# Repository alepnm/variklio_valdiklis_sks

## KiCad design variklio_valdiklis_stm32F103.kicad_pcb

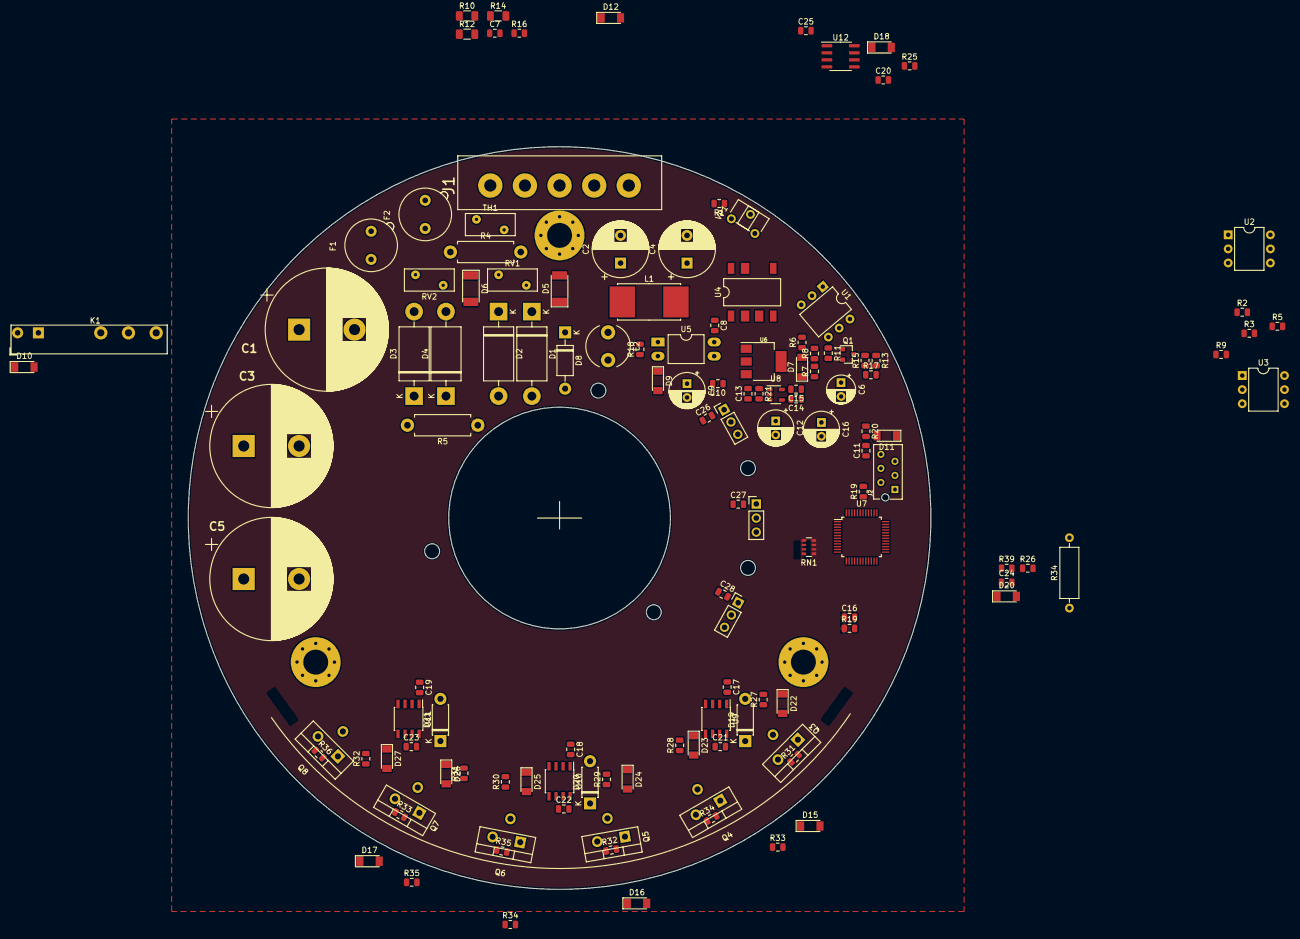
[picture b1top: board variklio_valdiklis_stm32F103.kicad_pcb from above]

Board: 2 copper layers, 134.0 x 134.0 mm, 131 parts (0 on the bottom side), 81 nets, no tracks yet.

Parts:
C1, C3, C5: 120x400V; CP_Radial_D22.0mm_P10.00mm_SnapIn
C2, C4: 4.7x400V; CP_Radial_D10.0mm_P5.00mm
C6: 1.0x50V; CP_Radial_D5.0mm_P2.50mm
C7, C8, C10, C11, C13, C14, C15, C16, C17, C18, C19: 100n; C_0805_2012Metric
C9, C12, C16#2: 100x16V; CP_Radial_D6.3mm_P2.50mm
C20, C24, C25: 1n0; C_0805_2012Metric
C21, C22, C23: 1.0uFx50V; C_0805_2012Metric
C26, C27, C28: 0.1; C_0805_2012Metric
D1, D2, D3, D4: D; D_DO-201AD_P15.24mm_Horizontal
D5, D6: LL4005; D_MELF
D7, D10, D11, D12, D15, D16, D17, D18, D20, D22, D23, D24, D25, D26, D27: LL4148; D_MiniMELF
D8: UF4005; D_DO-41_SOD81_P10.16mm_Horizontal
D9: 12V; D_MiniMELF
D19, D20#2, D21: LL4005; D_DO-41_SOD81_P7.62mm_Horizontal
F1: 5A; Fuseholder_TR5_Littelfuse_No560_No460
F2: 3A; Fuseholder_TR5_Littelfuse_No560_No460
H1: SA; PinHeader_1x03_P2.54mm_Vertical
H2: SB; PinHeader_1x03_P2.54mm_Vertical
H3: SC; PinHeader_1x03_P2.54mm_Vertical
J1: Conn_01x05; Jungtis
J2: ISP_SWD_Connector
K1: Omron; Relay_SPDT_Finder_34.51_Vertical
L1: 1mH; L_Vishay_IHSM-3825
L2: 1mH/280mA; L_Radial_D7.8mm_P5.00mm_Fastron_07HCP
Q1: BC807; SOT-23
Q3, Q4, Q5, Q6, Q7, Q8: IRF830; TO-220-3_Vertical
R1: 1k; R_0805_2012Metric
R2, R9: 1k0; R_0805_2012Metric
R3, R5, R8, R20, R21, R25: 10k; R_0805_2012Metric
R4: 8R2/2W; R_Axial_DIN0411_L9.9mm_D3.6mm_P12.70mm_Horizontal
R5#2: 220k; R_Axial_DIN0411_L9.9mm_D3.6mm_P12.70mm_Horizontal
R6: 490; R_0805_2012Metric
R7: 20k; R_0805_2012Metric
R10, R12, R14: 100k; R_1206_3216Metric
R11: 1M; R_0805_2012Metric
R13: 2.2k; R_0805_2012Metric
R15: 33k; R_0805_2012Metric
R16: 2k2; R_0805_2012Metric
R17: 22k; R_0805_2012Metric
R18: 4k7; R_0805_2012Metric
R19: 100k; R_0805_2012Metric
R19#2, R31#2, R32#2, R33, R34, R35, R36, R39: 1K0; R_0805_2012Metric
R26: 2k0; R_0805_2012Metric
R27, R28, R29, R30, R31, R32: 47R; R_0805_2012Metric
R33#2, R34#3, R35#2: 30R; R_0805_2012Metric
R34#2: 0R1; R_Axial_DIN0309_L9.0mm_D3.2mm_P12.70mm_Horizontal
RN1: 1k0; R_Array_Convex_4x0603
RV1, RV2: Varistor; RV_Disc_D9mm_W4mm_P5mm
TH1: 33R; RV_Disc_D9mm_W4mm_P5mm
U1, U2, U3: CNY17-1; DIP-6_W7.62mm
U4: LNK304G; PowerIntegrations_SMD-8B
U5: PC817; DIP-4_W10.16mm_LongPads
U6: LM340MP-5.0; LM340_SOT-223
U7: STM32F103C8Tx; LQFP-48_7x7mm_P0.5mm
U8: SIP21106; SOT-23-5
U9, U10, U11: IR2101; SOIC-8_3.9x4.9mm_P1.27mm
U12: ACS712; SOIC-8_3.9x4.9mm_P1.27mm
VP1: R_POT_TRIM; Potentiometer_ACP_CA6-H2,5_Horizontal

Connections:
/3VDC: C15.2, C16#2.1, D11.1, D12.1, D20.1, J2.5, R20.1, RN1.5, RN1.6, RN1.7, RN1.8, U2.5, U7.1, U7.9, U7.24, U7.36, U7.48, U8.5
/5VDC: C12.1, C13.2, C25.2, R21.1, U6.3, U8.1, U12.8
/ACL: F1.2, F2.2, J1.1
/ACN: D6.1, J1.2, RV2.2, TH1.2
/ADCVB: C7.2, D12.2, R14.2, R16.2
/CHA: U7.29, U9.2
/CHAN: U7.17, U9.3
/CHB: U7.30, U10.2
/CHBN: U7.18, U10.3
/CHC: U7.31, U11.2
/CHCN: U7.19, U11.3
/CURR: C20.2, D18.1, D20.2, R39.2, U7.13
/OKM: J1.4, U1.2
/OKP: J1.5, R1.2
/PHA: Q3.3, Q4.2, R31#2.1, R33#2.1
/PHB: Q5.3, Q6.2, R32#2.1, R34#3.1
/PHC: Q7.3, Q8.2, R33.1, R35#2.1
/RX: R3.1, U3.4
/RXD: R5.1, U2.4, U7.43
/SA: H1.2, RN1.3, U7.10
/SB: H2.2, RN1.2, U7.11
/SC: H3.2, RN1.1, U7.12
/SPEED: C6.1, R15.1, R17.1, U7.15
/SWDCLK: J2.3, U7.37
/SWDIO: J2.1, U7.34
/TEMP: C16.2, R19#2.2, U7.14
/TXD: R9.1, U7.42
/VB: K1.11, Q3.2, Q5.2, Q7.2
/VCC: C9.1, C10.2, C17.2, C18.2, C19.2, C26.2, C27.2, C28.2, D7.2, D10.1, D15.2, D16.2, D17.2, H1.1, H2.1, H3.1, K1.A1, L2.2, R6.1, R18.2, U5.1, U6.1, U9.1, U10.1, U11.1
/~NRST: C11.2, D11.2, J2.4, R20.2, U7.7
GND: C16.1, R3.2, R5#2.1, R19#2.1, R34#2.1, R39.1, U2.2
GNDD: C1.2, C2.2, C3.2, C4.2, C5.2, C6.2, C7.1, C9.2, C10.1, C11.1, C12.2, C13.1, C14.1, C15.1, C16#2.2, C17.1, C18.1, C19.1, C20.1, C24.1, C25.1, C26.1, C27.1, C28.1, D1.2, D2.2, D6.2, D8.2, D9.2, D19.2, D20#2.2, D21.2, H1.3, H2.3, H3.3, J2.2, J2.6, R5.2, R8.2, R13.2, R16.1, R17.2, R19.2, R25.2, U3.2, U6.2, U7.8, U7.23, U7.35, U7.47, U8.2, U9.4, U10.4, U11.4, U12.3, U12.4, U12.5
unnamed: C1.1, C3.1, C5.1, D3.1, D4.1, K1.14, R5#2.2, R10.1
unnamed: C2.1, D5.1, L1.1
unnamed: C4.1, L1.2, U4.5
unnamed: C8.1, D8.1, L2.1, U4.1, U4.2, U4.7, U4.8
unnamed: C8.2, U4.3, U5.4
unnamed: C14.2, U8.4
unnamed: C21.1, D19.1, R33#2.2, U9.6
unnamed: C21.2, D15.1, U9.8
unnamed: C22.1, D20#2.1, R34#3.2, U10.6
unnamed: C22.2, D16.1, U10.8
unnamed: C23.1, D21.1, R35#2.2, U11.6
unnamed: C23.2, D17.1, U11.8
unnamed: C24.2, U12.6
unnamed: D1.1, D3.2, F1.1, RV1.1
unnamed: D2.1, D4.2, RV1.2, TH1.1
unnamed: D5.2, R4.2
unnamed: D7.1, R7.1
unnamed: D9.1, R18.1, U5.2
unnamed: D10.2, K1.A2
unnamed: D18.2, R25.1, R26.2, R31#2.2
unnamed: D22.1, R27.2, U9.7
unnamed: D22.2, Q3.1, R27.1, R33.2
unnamed: D23.1, R28.2, U9.5
unnamed: D23.2, Q4.1, R28.1, R36.2
unnamed: D24.1, R29.2, U10.7
unnamed: D24.2, Q5.1, R29.1
unnamed: D25.1, R30.2, U10.5
unnamed: D25.2, Q6.1, R30.1
unnamed: D26.1, R31.2, U11.7
unnamed: D26.2, Q7.1, R31.1
unnamed: D27.1, R32.2, U11.5
unnamed: D27.2, Q8.1, R32.1
unnamed: F2.1, R4.1, RV2.1
unnamed: Q1.1, R7.2, R8.1, R11.2
unnamed: Q1.2, R11.1, U1.4
unnamed: Q1.3, R13.1, R15.2
unnamed: R34.1, R34#2.2, R35.1, R36.1
unnamed: Q4.3, Q6.3, Q8.3, U12.1, U12.2
unnamed: R1.1, VP1.1
unnamed: R2.1, U2.1
unnamed: R6.2, U1.5
unnamed: R9.2, U3.1
unnamed: R10.2, R12.1
unnamed: R12.2, R14.1
unnamed: R19.1, U7.44
unnamed: R21.2, U8.3
unnamed: R26.1, U12.7
unnamed: U1.1, VP1.2, VP1.3
unnamed: U4.4, U5.3

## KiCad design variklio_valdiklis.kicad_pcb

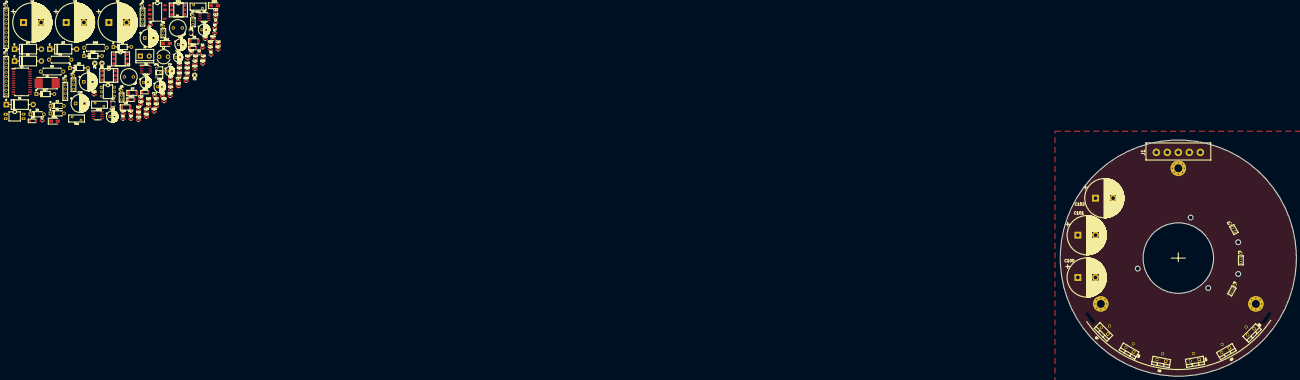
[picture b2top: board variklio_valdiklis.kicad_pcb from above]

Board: 2 copper layers, 134.0 x 134.0 mm, 138 parts (0 on the bottom side), 75 nets, no tracks yet.

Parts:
C1: 22n; C_0805_2012Metric
C2, C4, C6: 120x400V; CP_Radial_D22.0mm_P10.00mm_SnapIn
C3, C5: 4.7x400V; CP_Radial_D10.0mm_P5.00mm
C7: 47n; C_0805_2012Metric
C8, C25: 10n; C_0805_2012Metric
C9: 1.0x50V; CP_Radial_D5.0mm_P2.50mm
C10: 100x16V; CP_Radial_D5.0mm_P2.50mm
C11, C15, C18, C19: 100n; C_0805_2012Metric
C12, C20: 100x16V; CP_Radial_D6.3mm_P2.50mm
C13, C14, C16, C17, C27, C28, C30: 0.1; C_0805_2012Metric
C21, C22, C23: 2n2; C_0805_2012Metric
C24: 4n7; C_0805_2012Metric
C26: 1.0x400V; CP_Radial_D10.0mm_P5.00mm
C29, C31, C32: 22x25V; CP_Radial_D6.3mm_P2.50mm
C100, C101, C102: 120.0x400V; CP_Radial_D22.0mm_P10.00mm_SnapIn
D1, D2, D3, D4: D; D_DO-201AD_P15.24mm_Horizontal
D5, D6, D7: LL4005; D_MELF
D8: UF4005; D_DO-41_SOD81_P10.16mm_Horizontal
D9: 12V; D_MiniMELF
D10, D11, D12: 1N5818; D_SMA
D13, D14, D15: LL4148; D_MiniMELF
D16, D17: MUR140; D_DO-41_SOD81_P10.16mm_Horizontal
F1: 5A; Fuseholder_TR5_Littelfuse_No560_No460
F2: 3A; Fuseholder_TR5_Littelfuse_No560_No460
H1: SA; PinHeader_1x03_P2.54mm_Vertical
H2: SB; PinHeader_1x03_P2.54mm_Vertical
H3: SC; PinHeader_1x03_P2.54mm_Vertical
H600, H601, H602: HALL; PinHeader_1x03_P2.54mm_Vertical
J1: Conn_01x05; Jungtis
J1#2, J3: HALLS; PinHeader_1x05_P2.54mm_Vertical
J2, J4: IF; PinHeader_1x10_P2.54mm_Vertical
J5: GND; PinHeader_1x04_P2.54mm_Vertical
J6: VB; TerminalBlock_bornier-2_P5.08mm
L1: 1mH; L_Vishay_IHSM-3825
L2: 1mH/280mA; L_Radial_D7.8mm_P5.00mm_Fastron_07HCP
P1, P2, P3: Conn_01x01; Pin_D1.0mm_L10.0mm
Q1: BC807; SOT-23
Q2, Q3, Q4, Q5, Q6, Q7: IRF830; TO-220-3_Vertical
R1, R25, R30: 1k; R_0805_2012Metric
R2: 7.5k; R_0805_2012Metric
R3: 8R2/2W; R_Axial_DIN0411_L9.9mm_D3.6mm_P12.70mm_Horizontal
R4: 490; R_0805_2012Metric
R5, R13: 33k; R_0805_2012Metric
R6, R16, R18: 20k; R_0805_2012Metric
R7, R19, R21: 10k; R_0805_2012Metric
R8: 220k; R_Axial_DIN0411_L9.9mm_D3.6mm_P12.70mm_Horizontal
R9, R31, R33, R35: 1M; R_0805_2012Metric
R10: 2.2k; R_0805_2012Metric
R11: 49k; R_0805_2012Metric
R12: 150k; R_0805_2012Metric
R14: 22k; R_0805_2012Metric
R15: 4.7k; R_0805_2012Metric
R17: 4.5k; R_0805_2012Metric
R20: 4k7; R_0805_2012Metric
R22, R23, R24: 1.8k; R_0805_2012Metric
R26, R37, R38, R39: 18k; R_0805_2012Metric
R27, R28, R29: 100R; R_0805_2012Metric
R32, R34, R36: 72R; R_0805_2012Metric
R40: 0.1/2W; R_Axial_DIN0411_L9.9mm_D3.6mm_P12.70mm_Horizontal
RV1, RV2: Varistor; RV_Disc_D9mm_W4mm_P5mm
TH1: 33R; RV_Disc_D9mm_W4mm_P5mm
U1: CNY17-1; DIP-6_W7.62mm
U2: MC33039; SOIC-8_3.9x4.9mm_P1.27mm
U3: LNK304G; PowerIntegrations_SMD-8B
U4: PC817; DIP-4_W10.16mm_LongPads
U5: MC33035; SOIC-24W_7.5x15.4mm_P1.27mm
U6: LM393; SOIC-8_3.9x4.9mm_P1.27mm
U7: SIP21106; SOT-23-5
U8: NE555; SOIC-8_3.9x4.9mm_P1.27mm
U9, U10, U11: MOC8204; DIP-6_W7.62mm_SMDSocket_SmallPads
VP1: R_POT_TRIM; Potentiometer_ACP_CA6-H2,5_Horizontal
Z1: 1N5352; D_DO-41_SOD81_P10.16mm_Horizontal
Z2, Z3, Z4: 1N4744; D_DO-41_SOD81_P7.62mm_Horizontal

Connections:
/3VDC: C19.2, C20.1, U7.5
/+U: C29.2, C31.2, C32.2, D16.2, J6.1
/+V: C100.1, C101.1, C102.1
/AB: D12.1, J2.1, J4.3, R29.2, R36.2, U5.21
/ACL: F1.2, F2.2
/ACN: D7.1, RV2.2, TH1.2
/AT: C22.2, J2.2, J4.4, U5.2, U11.2
/BB: D11.1, J2.3, J4.5, R28.2, R34.2, U5.20
/BT: C21.2, J2.4, J4.6, U5.1, U10.2
/CB: D10.1, J2.5, J4.7, R27.2, R32.2, U5.19
/CT: C23.2, J2.6, J4.8, U5.24, U9.2
/OKM: J1.5, U1.2
/OKP: J1.4, R1.2
/SENS: C24.2, J2.9, J4.9, R25.2, R30.2, U5.9
/VB: C2.1, C4.1, C6.1, D3.1, D4.1, R8.2
/VCC: C10.1, C12.1, C13.2, C14.2, C15.2, C16.1, C17.1, C27.2, C28.2, C30.2, D5.2, H1.1, H2.1, H3.1, H600.1, H601.1, H602.1, J1#2.1, J3.1, J4.1, J4.2, L2.2, R2.1, R4.1, R15.2, R16.1, R18.1, R20.2, R21.1, R22.1, R24.1, U2.8, U4.1, U5.8, U5.17, U5.18, U5.22, U6.8, U7.1, U8.4, U8.8
/~SA: H1.2, J1#2.2, J3.2, U2.1, U5.4
/~SB: H2.2, J1#2.3, J3.3, U2.3, U5.5
/~SC: H3.2, J1#2.4, J3.4, U2.2, U5.6
GND: C1.1, C2.2, C3.2, C4.2, C5.2, C6.2, C8.1, C9.2, C12.2, C13.1, C14.1, C15.1, C16.2, C17.2, C18.1, C19.1, C20.2, C21.1, C22.1, C23.1, C24.1, C25.1, C27.1, C28.1, C30.1, D1.2, D2.2, D7.2, D8.2, D9.2, D10.2, D11.2, D12.2, H1.3, H2.3, H3.3, H600.3, H601.3, H602.3, J1#2.5, J2.10, J3.5, J4.10, J5.1, J5.2, J5.3, J6.2, R7.2, R8.1, R10.2, R14.2, R17.2, R25.1, R40.2, U2.7, U5.3, U5.15, U5.16, U5.23, U6.4, U7.2, U8.1, Z1.2
unnamed: C1.2, R2.2, U2.6
unnamed: C3.1, D6.1, L1.1
unnamed: C5.1, L1.2, U3.5
unnamed: C7.1, R5.2, R11.1, R12.2
unnamed: C7.2, R12.1, U5.13
unnamed: C8.2, R15.1, U5.10
unnamed: C9.1, R13.1, R14.1, U5.11
unnamed: C10.2, R19.1, U5.7
unnamed: C11.1, D8.1, L2.1, U3.1, U3.2, U3.7, U3.8
unnamed: C11.2, U3.3, U4.4
unnamed: C18.2, U7.4
unnamed: C25.2, R26.2, U8.6
unnamed: C26.1, D16.1, D17.2
unnamed: C26.2, R26.1, U8.2, U8.3, Z1.1
unnamed: C29.1, C31.1, C32.1, D17.1, U11.5
unnamed: C100.2, C101.2, C102.2
unnamed: D1.1, D3.2, F1.1, RV1.1
unnamed: D2.1, D4.2, RV1.2, TH1.1
unnamed: D5.1, R6.1
unnamed: D6.2, R3.2
unnamed: D9.1, R20.1, U4.2
unnamed: D13.1, R27.1
unnamed: D13.2, Q3.1, R32.1
unnamed: D14.1, R28.1
unnamed: D14.2, Q5.1, R34.1
unnamed: D15.1, R29.1
unnamed: D15.2, Q7.1, R36.1
unnamed: F2.1, R3.1, RV2.1
unnamed: P1.1, Q4.3, Q5.2, R38.1, Z3.2
unnamed: P2.1, Q2.3, Q3.2, R37.1, Z2.2
unnamed: P3.1, Q6.3, Q7.2, R39.1, Z4.2
unnamed: Q1.1, R6.2, R7.1, R9.2
unnamed: Q1.2, R9.1, U1.4
unnamed: Q1.3, R10.1, R13.2
unnamed: Q2.1, R31.2, R37.2, U9.4, Z2.1
unnamed: Q3.3, Q5.3, Q7.3, R30.1, R40.1
unnamed: Q4.1, R33.2, R38.2, U10.4, Z3.1
unnamed: Q6.1, R35.2, R39.2, U11.4, Z4.1
unnamed: R1.1, VP1.1
unnamed: R4.2, U1.5
unnamed: R5.1, U2.5
unnamed: R11.2, U5.12
unnamed: R16.2, R17.1, U6.2
unnamed: R18.2, U6.3
unnamed: R19.2, U5.14, U6.1
unnamed: R21.2, U7.3
unnamed: R22.2, U10.1
unnamed: R23.2, U11.1
unnamed: R24.2, U9.1
unnamed: R31.1, U9.6
unnamed: R33.1, U10.6
unnamed: R35.1, U11.6
unnamed: U1.1, VP1.2, VP1.3
unnamed: U3.4, U4.3
unnamed: U9.5, U10.5

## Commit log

2019-09-01 inicializacija
2019-09-03 schemos ir pcb paruosimas
2019-09-04 schemos ir plokstes analize
2019-09-05 schemos ir pcb ruosimas
2019-09-05 schemos paruosimas
2019-09-15 plokstes paruosimas, nauji pdf-ai
2019-09-29 schemos ir plokstes paruosimas
2019-10-09 schema stm32f103c8t
2019-10-09 stm32f103c8tx schemos ir plokstes ruosimas
2019-10-10 2019.10.10
2019-10-11 plokstes testavimams
